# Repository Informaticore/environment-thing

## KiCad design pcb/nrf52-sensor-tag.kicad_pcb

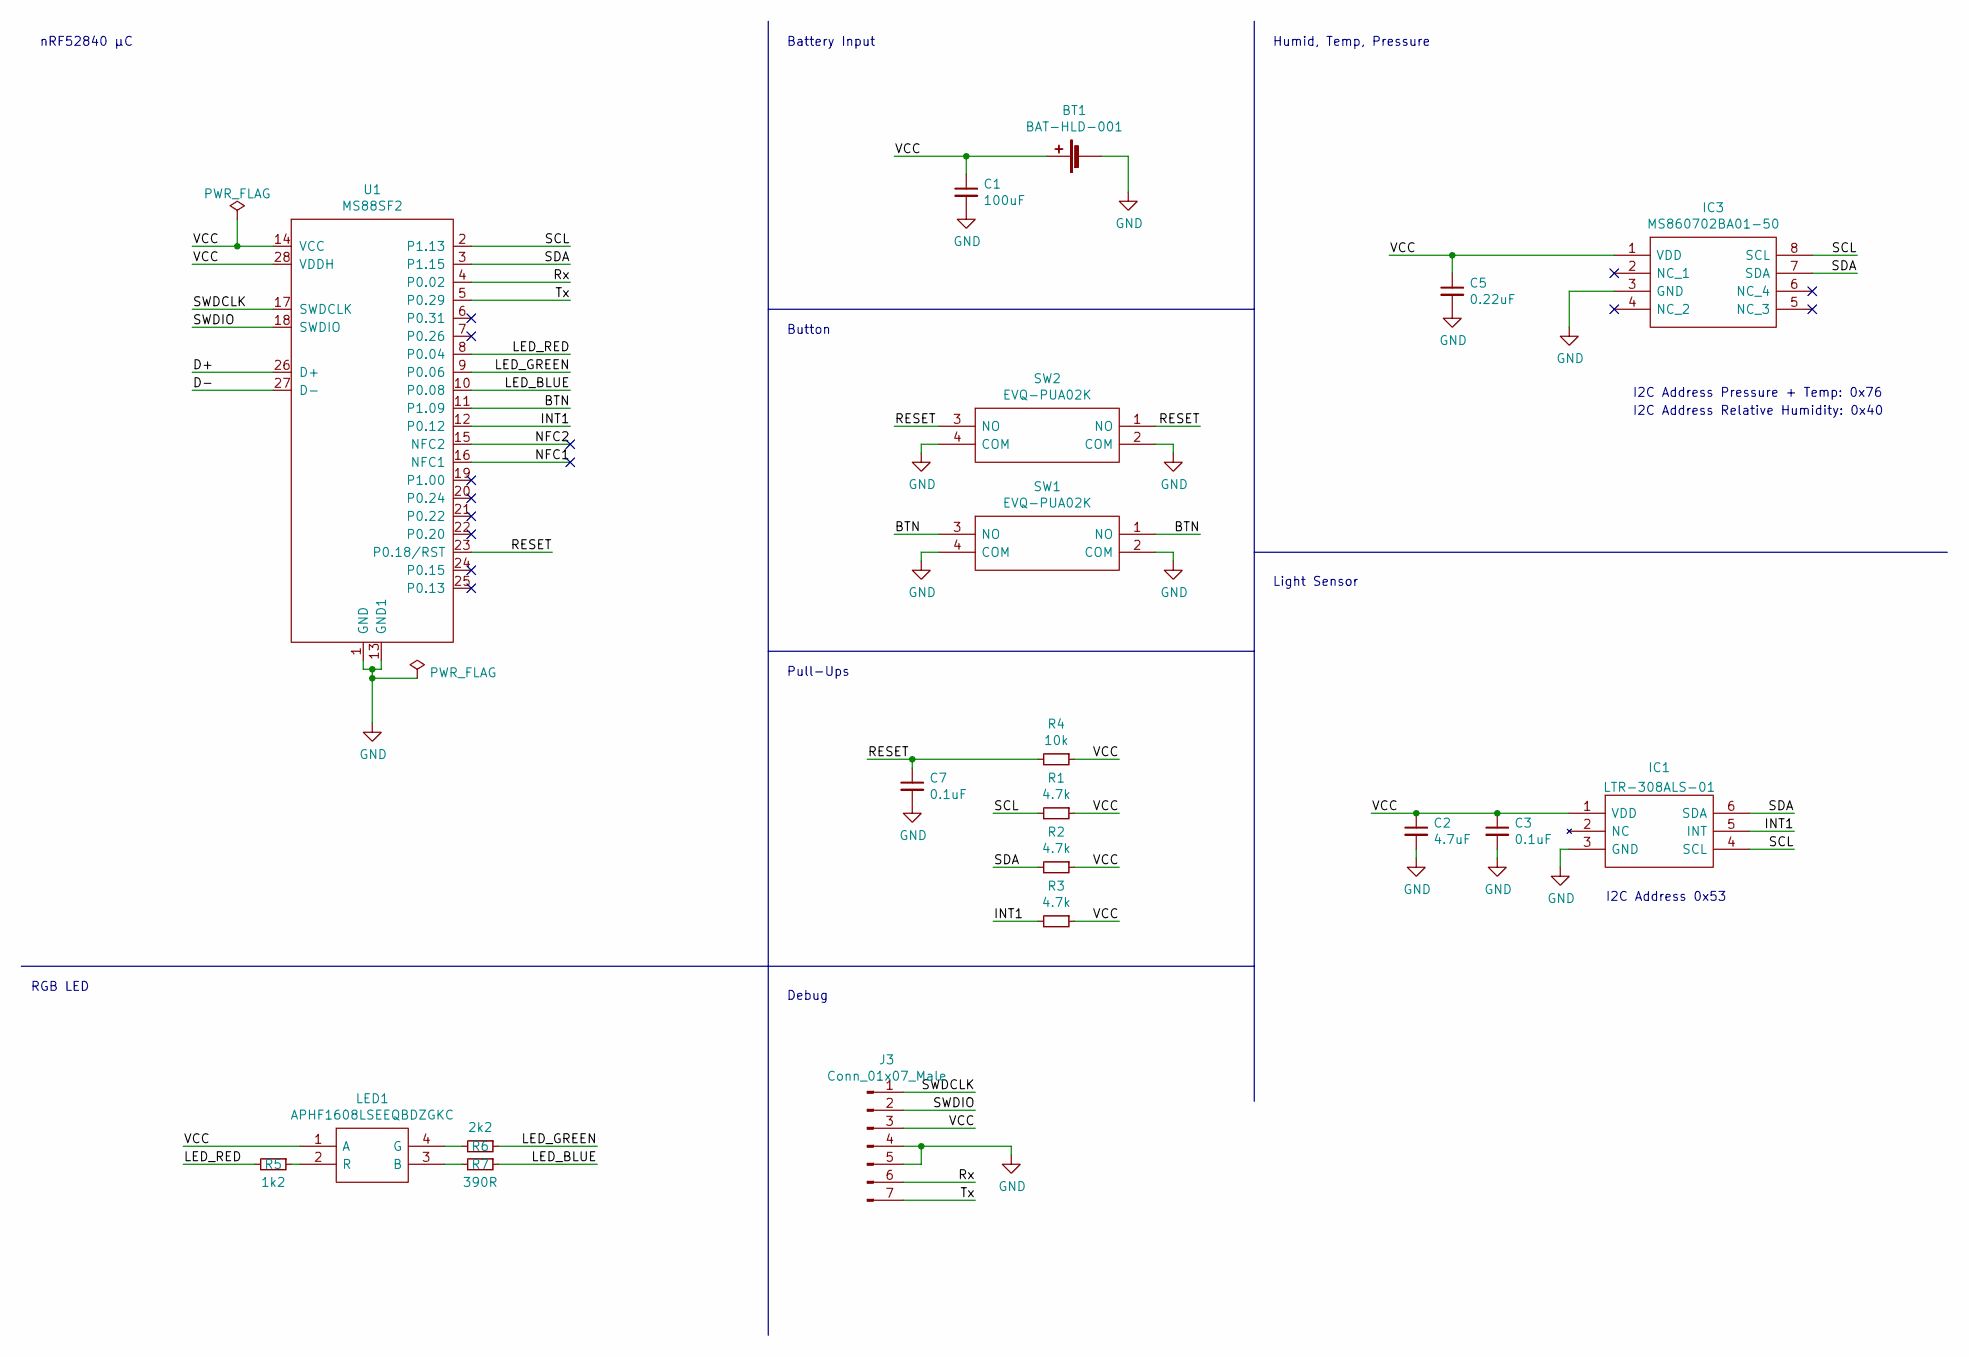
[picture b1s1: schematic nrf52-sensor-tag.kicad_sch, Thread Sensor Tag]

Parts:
BT1: BAT-HLD-001; BATHLD001
C1: 100uF; C_1210_3225Metric
C2: 4.7uF; C_0603_1608Metric
C3, C7: 0.1uF; C_0603_1608Metric
C5: 0.22uF; C_0603_1608Metric
IC1: LTR-308ALS-01; LTR303ALS01; Manufacturer_Part_Number LTR-308ALS-01; Mouser Part Number N/A
IC3: MS860702BA01-50; SON125P300X500X100-8N; Manufacturer_Part_Number MS860702BA01-50; Mouser Part Number 824-MS860702BA01-50
J3: Conn_01x07_Male; PinHeader_1x07_P2.54mm_Vertical
LED1: APHF1608LSEEQBDZGKC; Manufacturer_Part_Number APHF1608LSEEQBDZGKC; Mouser Part Number 604-APHF1608LQBDZGKC
R1, R2, R3: 4.7k; R_0603_1608Metric
R4: 10k; R_0603_1608Metric
R5: 1k2; R_0603_1608Metric
R6: 2k2; R_0603_1608Metric
R7: 390R; R_0603_1608Metric
SW1, SW2: EVQ-PUA02K; EVQPUA02K; Manufacturer_Part_Number EVQ-PUA02K; Mouser Part Number 667-EVQ-PUA02K
U1: MS88SF2

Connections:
/BTN: SW1.1 (NO), SW1.3 (NO), U1.11 (P1.09)
/D+: U1.26 (D+)
/D-: U1.27 (D-)
/INT1: IC1.5 (INT), R3.2, U1.12 (P0.12)
/LED_BLUE: R7.1, U1.10 (P0.08)
/LED_GREEN: R6.1, U1.9 (P0.06)
/LED_RED: R5.2, U1.8 (P0.04)
/NFC1: U1.16 (NFC1)
/NFC2: U1.15 (NFC2)
/RESET: C7.1, R4.2, SW2.1 (NO), SW2.3 (NO), U1.23 (P0.18/RST)
/Rx: J3.6, U1.4 (P0.02)
/SCL: IC1.4 (SCL), IC3.8 (SCL), R1.2, U1.2 (P1.13)
/SDA: IC1.6 (SDA), IC3.7 (SDA), R2.2, U1.3 (P1.15)
/SWDCLK: J3.1, U1.17 (SWDCLK)
/SWDIO: J3.2, U1.18 (SWDIO)
/Tx: J3.7, U1.5 (P0.29)
/VCC: BT1.1 (+), C1.1, C2.1, C3.1, C5.1, IC1.1 (VDD), IC3.1 (VDD), J3.3, LED1.1 (A), R1.1, R2.1, R3.1, R4.1, U1.14 (VCC), U1.28 (VDDH)
GND: BT1.2 (-), C1.2, C2.2, C3.2, C5.2, C7.2, IC1.3 (GND), IC3.3 (GND), J3.4, J3.5, SW1.2 (COM), SW1.4 (COM), SW2.2 (COM), SW2.4 (COM), U1.1 (GND), U1.13 (GND1)
unnamed: LED1.2 (R), R5.1
unnamed: LED1.3 (B), R7.2
unnamed: LED1.4 (G), R6.2

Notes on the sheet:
Humid, Temp, Pressure
nRF52840 µC
Pull-Ups
RGB LED
Battery Input
I2C Address Pressure + Temp: 0x76
Button
I2C Address 0x53
Debug
I2C Address Relative Humidity: 0x40
Light Sensor

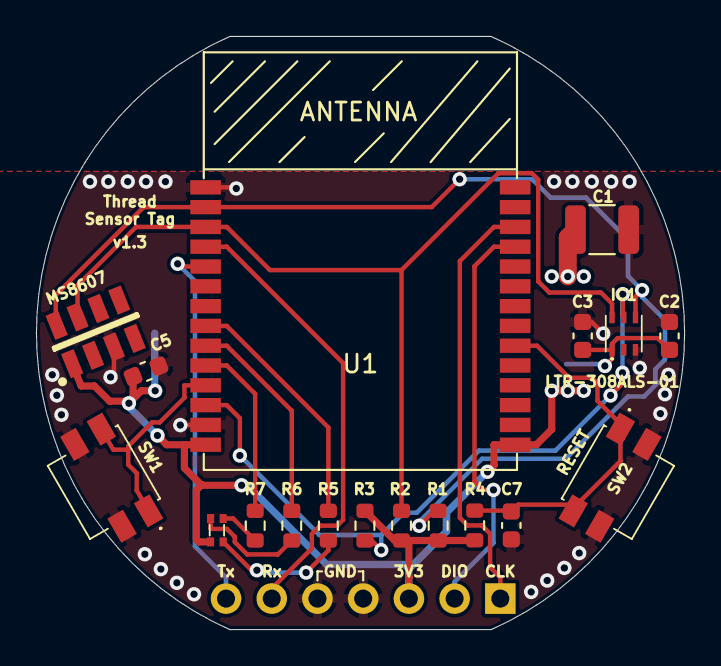
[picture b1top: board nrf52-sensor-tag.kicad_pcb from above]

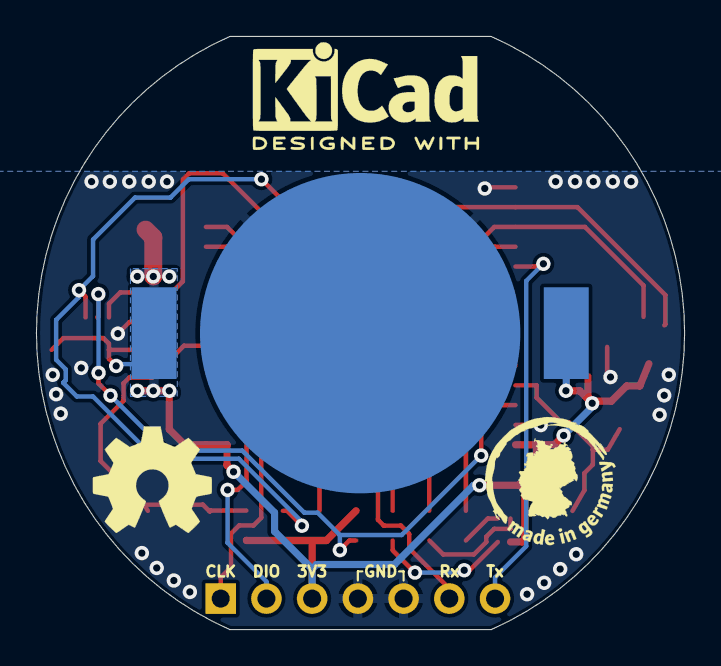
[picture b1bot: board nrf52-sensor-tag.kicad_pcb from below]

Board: 2 copper layers, 36.0 x 33.0 mm, 23 parts (5 on the bottom side), 17 nets.

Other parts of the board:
LOGO1: OSHW-Symbol_6.7x6mm_SilkScreen
LOGO2: LOGO; mig
LOGO3: KiCad-Logo2_5mm_SilkScreen

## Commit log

2022-10-08 Added PCB KiCad data
2022-10-08 Added PWR_FLAG to power tracks
2022-10-08 Fixed DRC issues

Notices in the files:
pcb/nrf52-sensor-tag.kicad_sch:
Licence: MIT
